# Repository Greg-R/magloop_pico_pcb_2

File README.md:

#  Printed Circuit Board for Magnetic Loop Antenna Controller Version 2

Design and fabrication files the Magnetic Loop Antenna Controller printed circuit board.

#  License

Please refer to the LICENSE file included in this repository.

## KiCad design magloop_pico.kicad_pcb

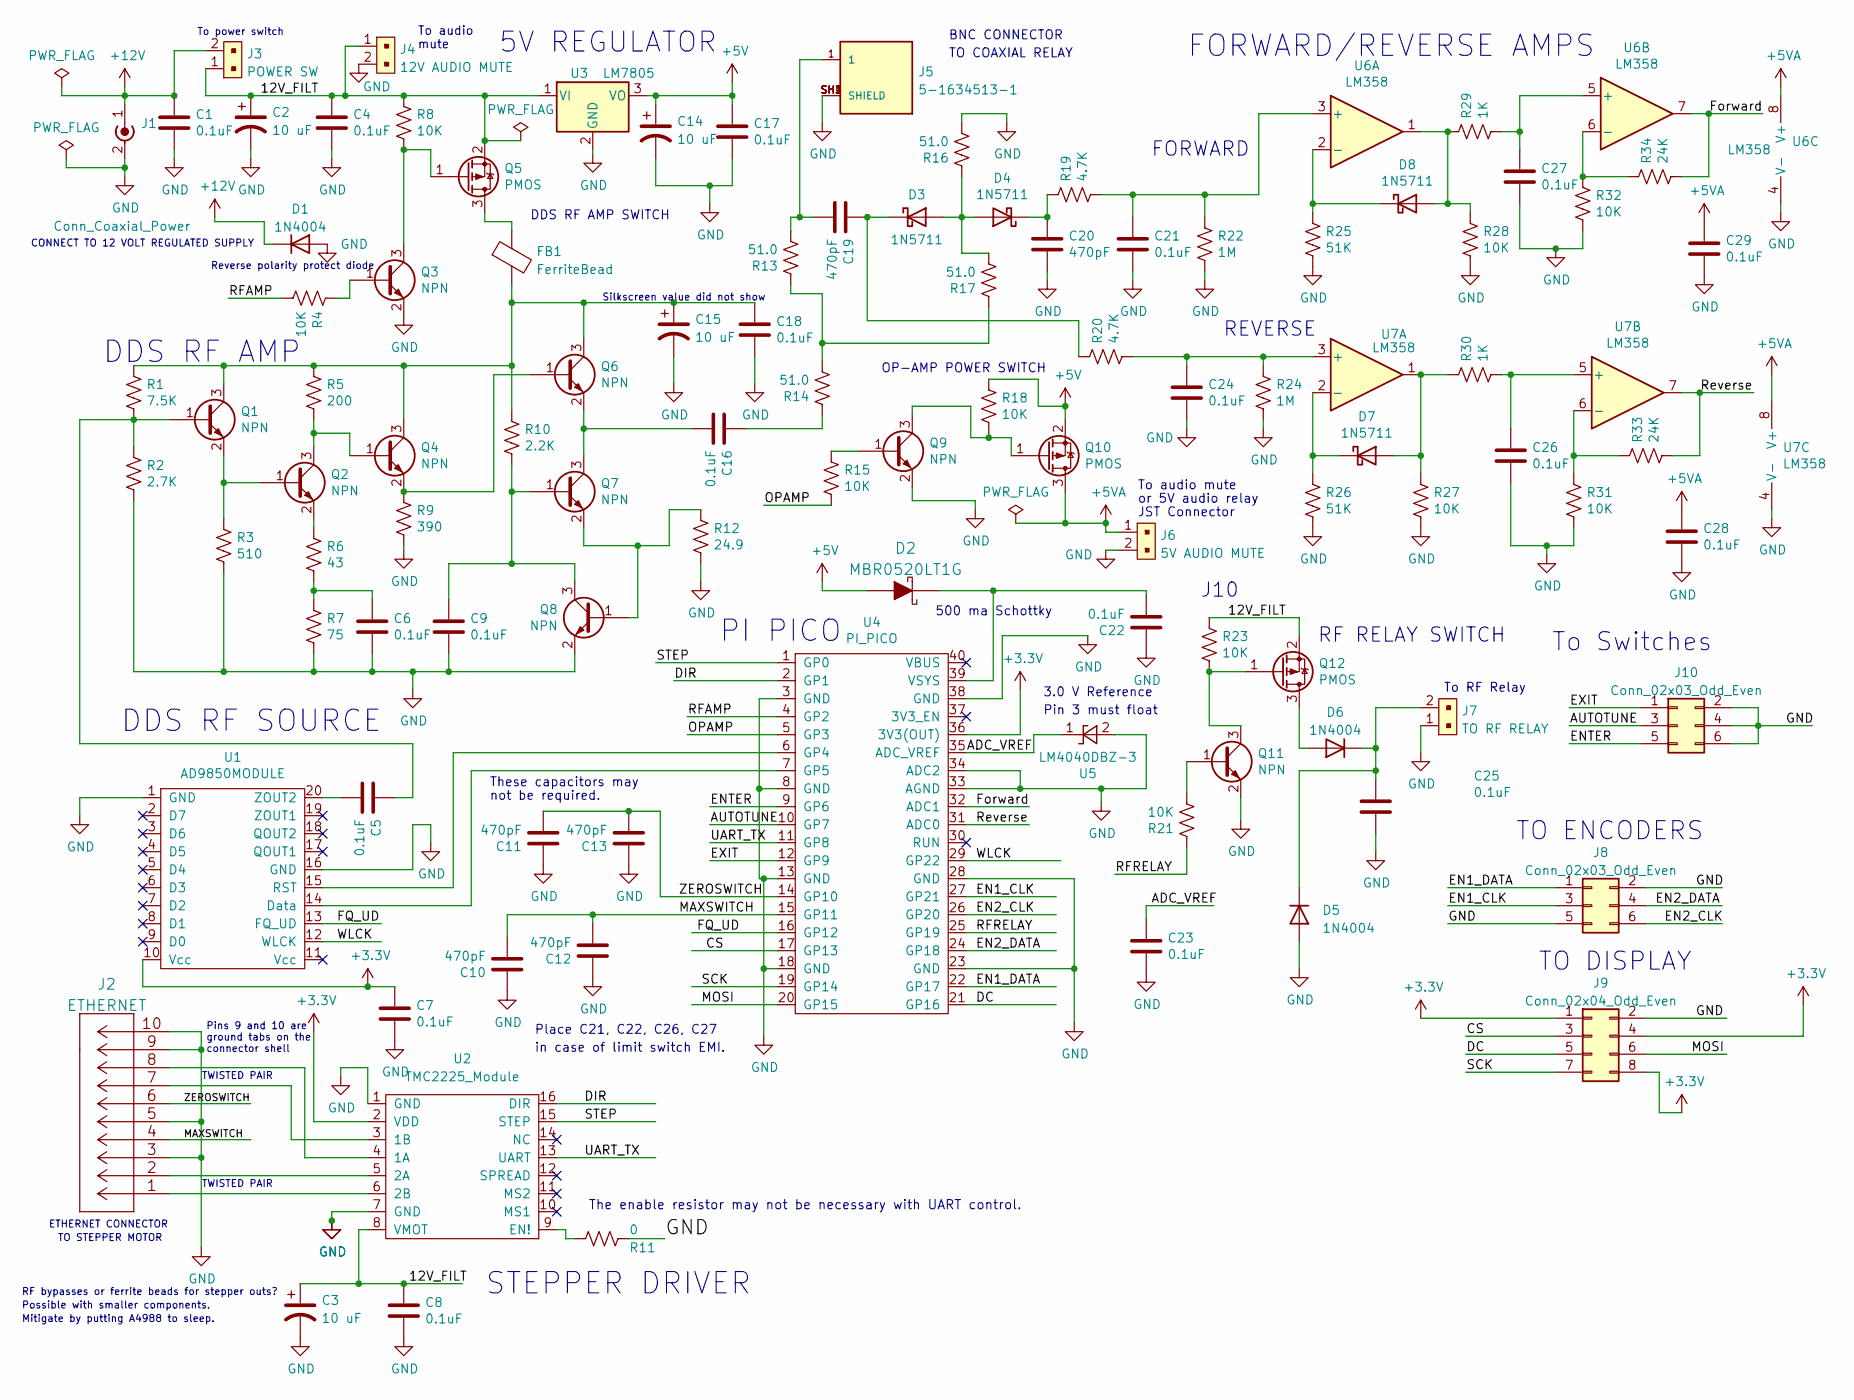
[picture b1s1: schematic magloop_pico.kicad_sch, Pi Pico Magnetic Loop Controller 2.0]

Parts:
C1, C4, C5, C6, C7, C8, C9, C16, C17, C18, C21, C22, C23, C24, C25, C26, C27, C28, C29: 0.1uF; C_1206_3216Metric_Pad1.33x1.80mm_HandSolder
C2, C3, C14, C15: 10 uF; CP_Radial_D5.0mm_P2.00mm
C10, C11, C12, C13, C19, C20: 470pF; C_1206_3216Metric_Pad1.33x1.80mm_HandSolder
D1, D5, D6: 1N4004; D_SMB
D2: MBR0520LT1G; SOD-123; MPN MBR0520LT1G; Digi-Key_PN MBR0520LT1GOSCT-ND
D3, D4, D7, D8: 1N5711; D_DO-35_SOD27_P7.62mm_Horizontal
FB1: FerriteBead; L_1206_3216Metric
J1: Conn_Coaxial_Power; BarrelJack_CUI_PJ-036AH-SMT_Horizontal
J2: ETHERNET; 2-406541-3
J3: POWER SW; PinHeader_1x2_P2.5mm_Drill1.1mm; MPN B2B-XH-A(LF)(SN); Digi-Key_PN 455-2247-ND
J4: 12V AUDIO MUTE; PinHeader_1x2_P2.5mm_Drill1.1mm; MPN B2B-XH-A(LF)(SN); Digi-Key_PN 455-2247-ND
J5: 5-1634513-1; TE_5-1634513-1
J6: 5V AUDIO MUTE; PinHeader_1x2_P2.5mm_Drill1.1mm; MPN B2B-XH-A(LF)(SN); Digi-Key_PN 455-2247-ND
J7: TO RF RELAY; PinHeader_1x2_P2.5mm_Drill1.1mm; MPN B2B-XH-A(LF)(SN); Digi-Key_PN 455-2247-ND
J8, J10: Conn_02x03_Odd_Even; IDC-Header_2x03_P2.54mm_Vertical
J9: Conn_02x04_Odd_Even; IDC-Header_2x04_P2.54mm_Vertical
Q1, Q2, Q3, Q4, Q6, Q7, Q8, Q9, Q11: NPN; SOT-23
Q5, Q10, Q12: PMOS; SOT-23
R1: 7.5K; R_1206_3216Metric_Pad1.30x1.75mm_HandSolder
R2: 2.7K; R_1206_3216Metric_Pad1.30x1.75mm_HandSolder
R3: 510; R_1206_3216Metric_Pad1.30x1.75mm_HandSolder
R4, R8, R15, R18, R21, R23, R27, R28, R31, R32: 10K; R_1206_3216Metric_Pad1.30x1.75mm_HandSolder
R5: 200; R_1206_3216Metric_Pad1.30x1.75mm_HandSolder
R6: 43; R_1206_3216Metric_Pad1.30x1.75mm_HandSolder
R7: 75; R_1206_3216Metric_Pad1.30x1.75mm_HandSolder
R9: 390; R_1206_3216Metric_Pad1.30x1.75mm_HandSolder
R10: 2.2K; R_1206_3216Metric_Pad1.30x1.75mm_HandSolder
R11: 0; R_1206_3216Metric_Pad1.30x1.75mm_HandSolder
R12: 24.9; R_1206_3216Metric_Pad1.30x1.75mm_HandSolder
R13, R14, R16, R17: 51.0; R_1206_3216Metric_Pad1.30x1.75mm_HandSolder
R19, R20: 4.7K; R_1206_3216Metric_Pad1.30x1.75mm_HandSolder
R22, R24: 1M; R_1206_3216Metric_Pad1.30x1.75mm_HandSolder
R25, R26: 51K; R_1206_3216Metric_Pad1.30x1.75mm_HandSolder
R29, R30: 1K; R_1206_3216Metric_Pad1.30x1.75mm_HandSolder
R33, R34: 24K; R_1206_3216Metric_Pad1.30x1.75mm_HandSolder
U1: AD9850MODULE; AD9850_MODULE
U2: TMC2225_Module; TMC2209_MODULE
U3: LM7805; TO-220-3_Vertical
U4: PI_PICO
U5: LM4040DBZ-3; SOT-23
U6, U7: LM358; SOIC-8_3.9x4.9mm_P1.27mm

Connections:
+3.3V: C7.1, J9.1, J9.4, J9.8, U1.10 (Vcc), U2.2 (VDD), U4.36 (3V3(OUT))
+5V: C14.1, C17.1, D2.A, Q10.2 (S), R18.1, U3.3 (VO)
+5VA: C28.1, C29.1, J6.1, Q10.3 (D), U6.8 (V+), U7.8 (V+)
+12V: C1.1, D1.1 (K), J1.1 (In), J3.2
/12V_FILT: C2.1, C3.1, C4.1, C8.1, J3.1, J4.1, Q5.2 (S), Q12.2 (S), R8.1, R23.1, U2.8 (VMOT), U3.1 (VI)
/ADC_VREF: C23.1, U4.35 (ADC_VREF), U5.1 (K)
/AUTOTUNE: J10.3, U4.10 (GP7)
/CS: J9.3, U4.17 (GP13)
/DC: J9.5, U4.21 (GP16)
/DIR: U2.16 (DIR), U4.2 (GP1)
/EN1_CLK: J8.3, U4.27 (GP21)
/EN1_DATA: J8.1, U4.22 (GP17)
/EN2_CLK: J8.6, U4.26 (GP20)
/EN2_DATA: J8.4, U4.24 (GP18)
/ENTER: J10.5, U4.9 (GP6)
/EXIT: J10.1, U4.12 (GP9)
/FQ_UD: U1.13 (FQ_UD), U4.16 (GP12)
/Forward: R34.2, U4.32 (ADC1), U6.7
/MAXSWITCH: C10.2, C12.2, J2.4, U4.15 (GP11)
/MOSI: J9.6, U4.20 (GP15)
/OPAMP: R15.2, U4.5 (GP3)
/RFAMP: R4.2, U4.4 (GP2)
/RFRELAY: R21.1, U4.25 (GP19)
/Reverse: R33.2, U4.31 (ADC0), U7.7
/SCK: J9.7, U4.19 (GP14)
/STEP: U2.15 (STEP), U4.1 (GP0)
/UART_TX: U2.13 (UART), U4.11 (GP8)
/WLCK: U1.12 (WLCK), U4.29 (GP22)
/ZEROSWITCH: C11.2, C13.2, J2.6, U4.14 (GP10)
GND: C1.2, C2.2, C3.2, C4.2, C6.2, C7.2, C8.2, C9.2, C10.1, C11.1, C12.1, C13.1, C14.2, C15.2, C17.2, C18.2, C20.2, C21.2, C22.1, C23.2, C24.2, C25.2, C26.2, C27.2, C28.2, C29.2, D1.2 (A), D5.2 (A), J1.2 (Ext), J2.3, J2.5, J2.9, J2.10, J4.2, J5.SH1 (SHIELD), J5.SH2 (SHIELD), J5.SH3 (SHIELD), J5.SH4 (SHIELD), J6.2, J7.1, J8.2, J8.5, J9.2, J10.2, J10.4, J10.6, Q3.2 (E), Q8.2 (E), Q9.2 (E), Q11.2 (E), R2.2, R3.2, R7.2, R9.2, R11.1, R12.2, R16.2, R22.2, R24.2, R25.2, R26.2, R27.2, R28.2, R31.2, R32.2, U1.1 (GND), U1.16 (GND), U2.1 (GND), U2.7 (GND), U3.2 (GND), U4.3 (GND), U4.8 (GND), U4.13 (GND), U4.18 (GND), U4.23 (GND), U4.28 (GND), U4.33 (AGND), U4.34 (ADC2), U4.38 (GND), U5.2 (A), U6.4 (V-), U7.4 (V-)
unnamed: C6.1, R6.2, R7.1
unnamed: C16.1, R14.1
unnamed: C19.2, J5.1, R13.2
unnamed: D3.2 (A), D4.2 (A), R16.1, R17.2
unnamed: C19.1, D3.1 (K), R20.1
unnamed: C20.1, D4.1 (K), R19.1
unnamed: C25.1, D5.1 (K), D6.1 (K), J7.2
unnamed: D6.2 (A), Q12.3 (D)
unnamed: D7.2 (A), R27.1, R30.1, U7.1
unnamed: D7.1 (K), R26.1, U7.2 (-)
unnamed: D8.2 (A), R28.1, R29.1, U6.1
unnamed: D8.1 (K), R25.1, U6.2 (-)
unnamed: C5.1, Q1.1 (B), R1.2, R2.1
unnamed: C15.1, C18.1, FB1.2, Q1.3 (C), Q4.3 (C), Q6.3 (C), R1.1, R5.1, R10.1
unnamed: Q1.2 (E), Q2.1 (B), R3.1
unnamed: Q2.3 (C), Q4.1 (B), R5.2
unnamed: Q2.2 (E), R6.1
unnamed: Q3.1 (B), R4.1
unnamed: Q3.3 (C), Q5.1 (G), R8.2
unnamed: Q4.2 (E), Q6.1 (B), R9.1
unnamed: FB1.1, Q5.3 (D)
unnamed: C16.2, Q6.2 (E), Q7.3 (C)
unnamed: C9.1, Q7.1 (B), Q8.3 (C), R10.2
unnamed: Q7.2 (E), Q8.1 (B), R12.1
unnamed: Q9.1 (B), R15.1
unnamed: Q9.3 (C), Q10.1 (G), R18.2
unnamed: Q11.1 (B), R21.2
unnamed: Q11.3 (C), Q12.1 (G), R23.2
unnamed: R13.1, R14.2, R17.1
unnamed: U1.14 (Data), U4.7 (GP5)
unnamed: U1.15 (RST), U4.6 (GP4)
unnamed: C5.2, U1.20 (ZOUT2)
unnamed: J2.8, U2.4 (1A)
unnamed: J2.7, U2.3 (1B)
unnamed: J2.2, U2.5 (2A)
unnamed: J2.1, U2.6 (2B)
unnamed: R11.2, U2.9 (EN!)
unnamed: C22.2, D2.K, U4.39 (VSYS)
unnamed: C21.1, R19.2, R22.1, U6.3 (+)
unnamed: C27.1, R29.2, U6.5 (+)
unnamed: R32.1, R34.1, U6.6 (-)
unnamed: C24.1, R20.2, R24.1, U7.3 (+)
unnamed: C26.1, R30.2, U7.5 (+)
unnamed: R31.1, R33.1, U7.6 (-)

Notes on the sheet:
To RF Relay
CONNECT TO 12 VOLT REGULATED SUPPLY
PI PICO
STEPPER DRIVER
To audio mute
JST Connector
BNC CONNECTOR
To Switches
Reverse polarity protect diode
DDS RF AMP SWITCH
or 5V audio relay
TWISTED PAIR
ETHERNET CONNECTOR
Silkscreen value did not show
TO STEPPER MOTOR
J10
RF bypasses or ferrite beads for stepper outs?
OP-AMP POWER SWITCH
5V REGULATOR
REVERSE
To audio
To power switch
DDS RF SOURCE
TO COAXIAL RELAY
Place C21, C22, C26, C27
TO ENCODERS
500 ma Schottky
FORWARD
DDS RF AMP
Pins 9 and 10 are ground tabs on the connector shell
These capacitors may
Possible with smaller components.
TO DISPLAY
Mitigate by putting A4988 to sleep.
FORWARD/REVERSE AMPS
Pin 3 must float
3.0 V Reference
mute
not be required.
RF RELAY SWITCH

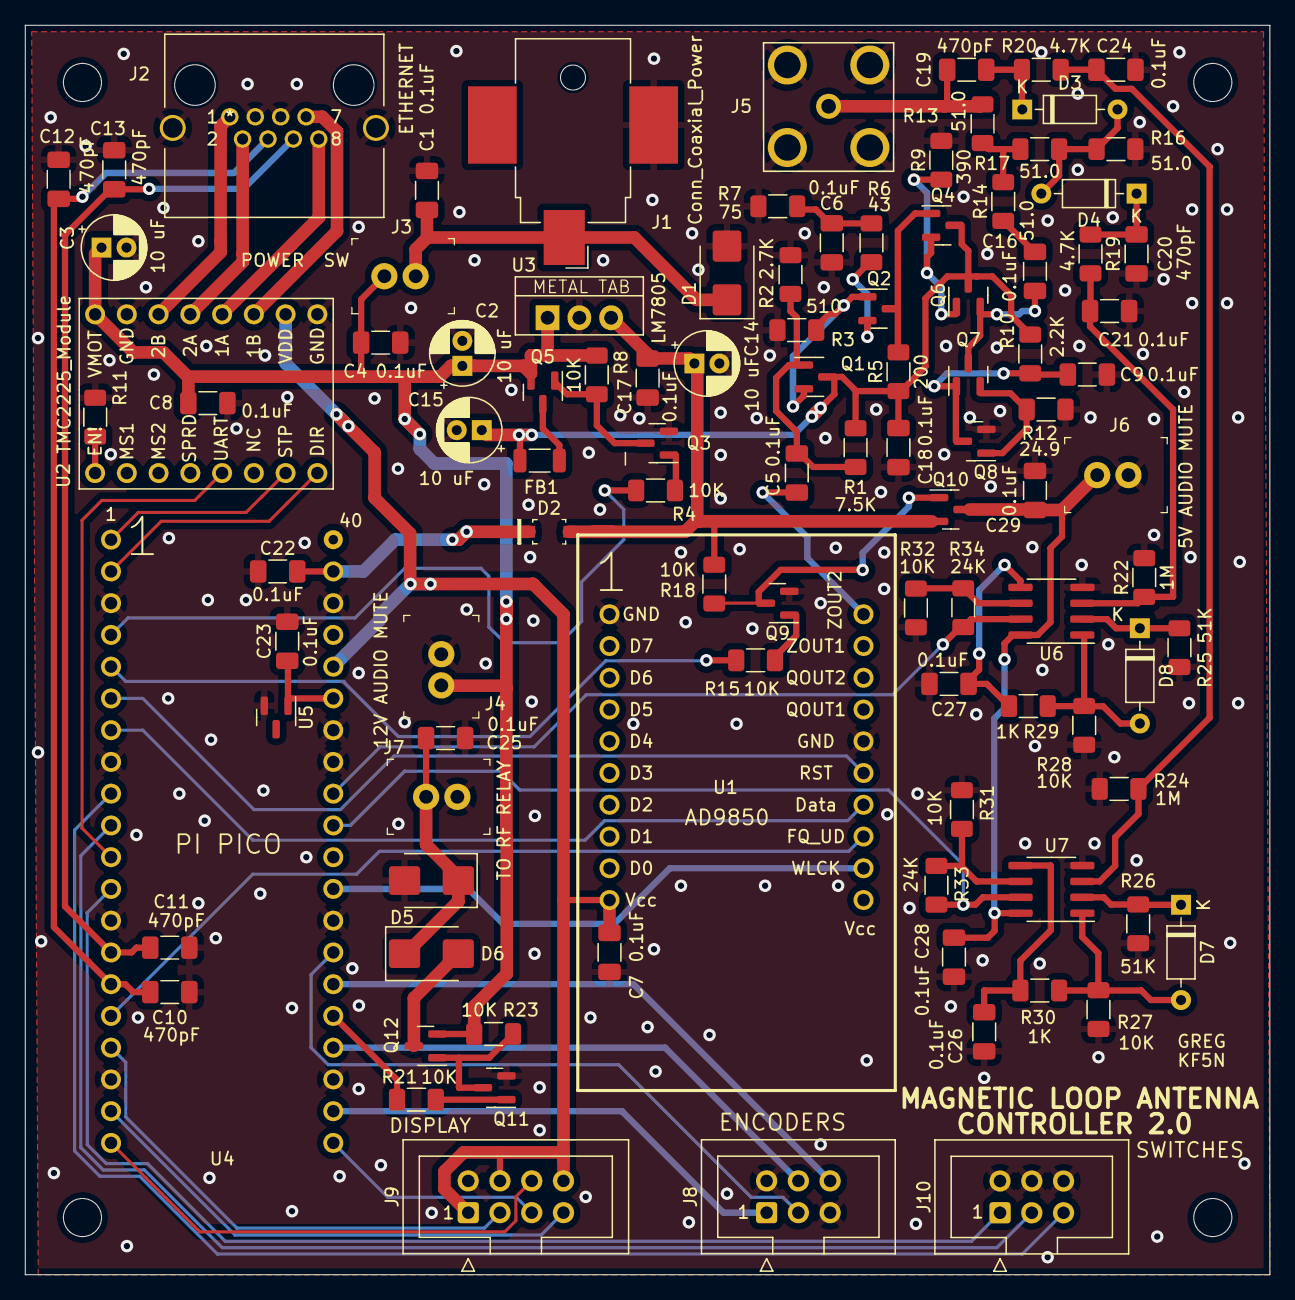
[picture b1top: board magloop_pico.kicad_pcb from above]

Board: 2 copper layers, 99.6 x 99.9 mm, 101 parts (0 on the bottom side), 74 nets.

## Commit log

2023-01-27 Root commit.
2023-01-27 Updated README.md.
2023-04-05 Got all nets wired. Not clean yet.
2023-04-06 Layout clean
2023-04-08 This commit prior to experiment re-ordering schematic designators.
2023-04-08 Seems to be clean. Wait another 24 hours before release.
2023-04-10 Released to PCBWay.
2023-05-27 Updated BOM to show 0.9 degree stepper motor, delete DIP switch.
2024-08-24 Fixed BOM problem with R5.

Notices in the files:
parts and their libraries:
Copyright 2021 Accelerated Designs. All rights reserved.
